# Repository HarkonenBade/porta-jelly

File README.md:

# porta-jelly

Rework of @cillian64 's excellent mini-jelly board (https://github.com/cillian64/cyberjelly/tree/master/mini_jellies/mini_jellies) tweaked to include an IP5306 based Lipo charge and boost setup to make a portable LED strip driving system with built in battery charging.

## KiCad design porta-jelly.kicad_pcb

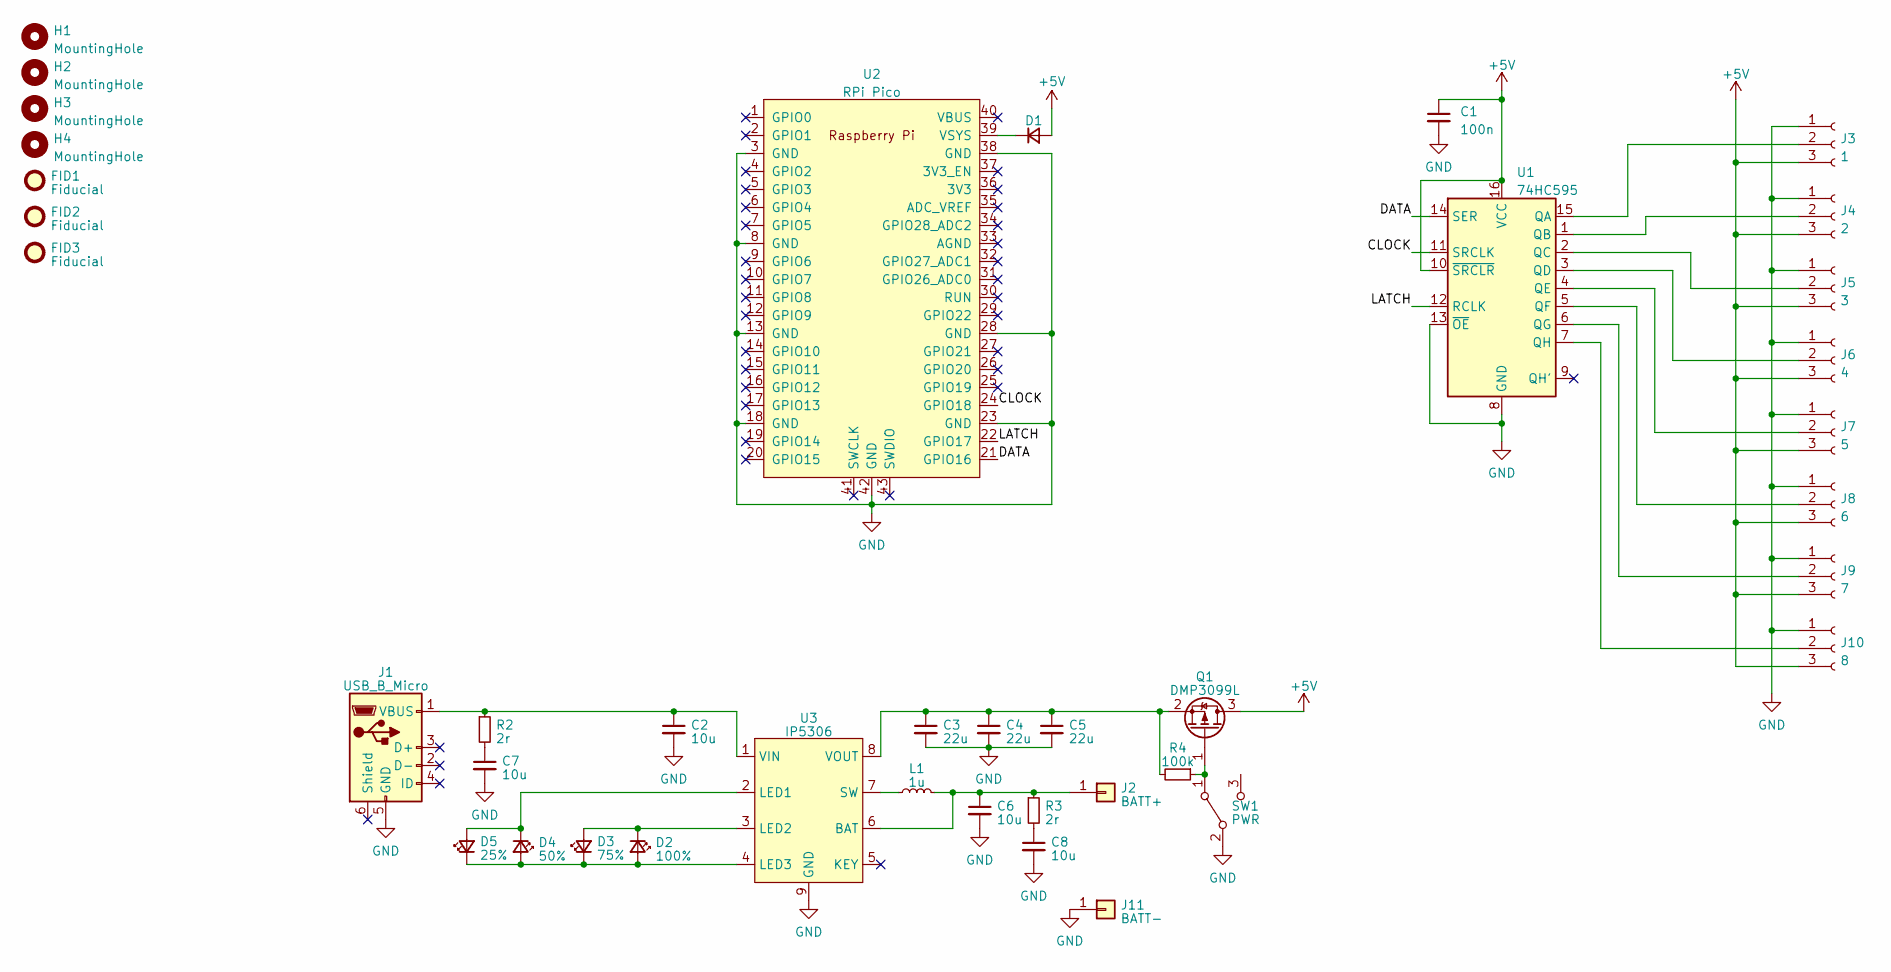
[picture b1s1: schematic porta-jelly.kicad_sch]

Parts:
C1: 100n; C_0603_1608Metric
C2, C6, C7, C8: 10u; C_0603_1608Metric; LCSC C19702
C3, C4, C5: 22u; C_0805_2012Metric; LCSC C159801
D1: D_Small; D_0805_2012Metric; LCSC C146335
D2: 100%; LED_0805_2012Metric; LCSC C497961
D3: 75%; LED_0805_2012Metric; LCSC C497961
D4: 50%; LED_0805_2012Metric; LCSC C497961
D5: 25%; LED_0805_2012Metric; LCSC C497961
FID1, FID2, FID3: Fiducial; Fiducial_1mm_Mask2mm
H1, H2, H3, H4: MountingHole; MountingHole_3.2mm_M3
J1: USB_B_Micro; USB_Micro-B_Molex-105017-0001; LCSC C136000
J2: BATT+; Bonded_Pad
J3: 1; Molex_KK-254_AE-6410-03A_1x03_P2.54mm_Vertical
J4: 2; Molex_KK-254_AE-6410-03A_1x03_P2.54mm_Vertical
J5: 3; Molex_KK-254_AE-6410-03A_1x03_P2.54mm_Vertical
J6: 4; Molex_KK-254_AE-6410-03A_1x03_P2.54mm_Vertical
J7: 5; Molex_KK-254_AE-6410-03A_1x03_P2.54mm_Vertical
J8: 6; Molex_KK-254_AE-6410-03A_1x03_P2.54mm_Vertical
J9: 7; Molex_KK-254_AE-6410-03A_1x03_P2.54mm_Vertical
J10: 8; Molex_KK-254_AE-6410-03A_1x03_P2.54mm_Vertical
J11: BATT-; Bonded_Pad
L1: 1u; LQH44PH1R0MPRL; LCSC C1857967
Q1: DMP3099L; SOT-23; LCSC C155244
R2, R3: 2r; R_0603_1608Metric; LCSC C307263
R4: 100k; R_0603_1608Metric
SW1: PWR; SK12D07VG5; LCSC C3020419
U1: 74HC595; SOIC-16_3.9x9.9mm_P1.27mm; LCSC C5947
U2: RPi Pico; RPi_Pico_SMD_TH
U3: IP5306; SOIC-8-1EP_3.9x4.9mm_P1.27mm_EP2.29x3mm_ThermalVias; LCSC C181692

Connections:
+5V: C1.1, D1.2 (A), J3.3, J4.3, J5.3, J6.3, J7.3, J8.3, J9.3, J10.3, Q1.3 (D), U1.10 (~SRCLR), U1.16 (VCC)
/CLOCK: U1.11 (SRCLK), U2.24 (GPIO18)
/DATA: U1.14 (SER), U2.21 (GPIO16)
/LATCH: U1.12 (RCLK), U2.22 (GPIO17)
GND: C1.2, C2.2, C3.2, C4.2, C5.2, C6.2, C7.2, C8.2, J1.5 (GND), J3.1, J4.1, J5.1, J6.1, J7.1, J8.1, J9.1, J10.1, J11.1, SW1.2 (B), U1.8 (GND), U1.13 (~OE), U2.3 (GND), U2.8 (GND), U2.13 (GND), U2.18 (GND), U2.23 (GND), U2.28 (GND), U2.38 (GND), U2.42 (GND), U3.9 (GND)
unnamed: C7.1, R2.2
unnamed: C8.1, R3.2
unnamed: D1.1 (K), U2.39 (VSYS)
unnamed: D2.2 (A), D3.1 (K), D4.2 (A), D5.1 (K), U3.4 (LED3)
unnamed: D2.1 (K), D3.2 (A), U3.3 (LED2)
unnamed: D4.1 (K), D5.2 (A), U3.2 (LED1)
unnamed: C2.1, J1.1 (VBUS), R2.1, U3.1 (VIN)
unnamed: C6.1, J2.1, L1.2, R3.1, U3.6 (BAT)
unnamed: J3.2, U1.15 (QA)
unnamed: J4.2, U1.1 (QB)
unnamed: J5.2, U1.2 (QC)
unnamed: J6.2, U1.3 (QD)
unnamed: J7.2, U1.4 (QE)
unnamed: J8.2, U1.5 (QF)
unnamed: J9.2, U1.6 (QG)
unnamed: J10.2, U1.7 (QH)
unnamed: Q1.1 (G), R4.1, SW1.1 (A)
unnamed: C3.1, C4.1, C5.1, Q1.2 (S), R4.2, U3.8 (VOUT)
unnamed: L1.1, U3.7 (SW)

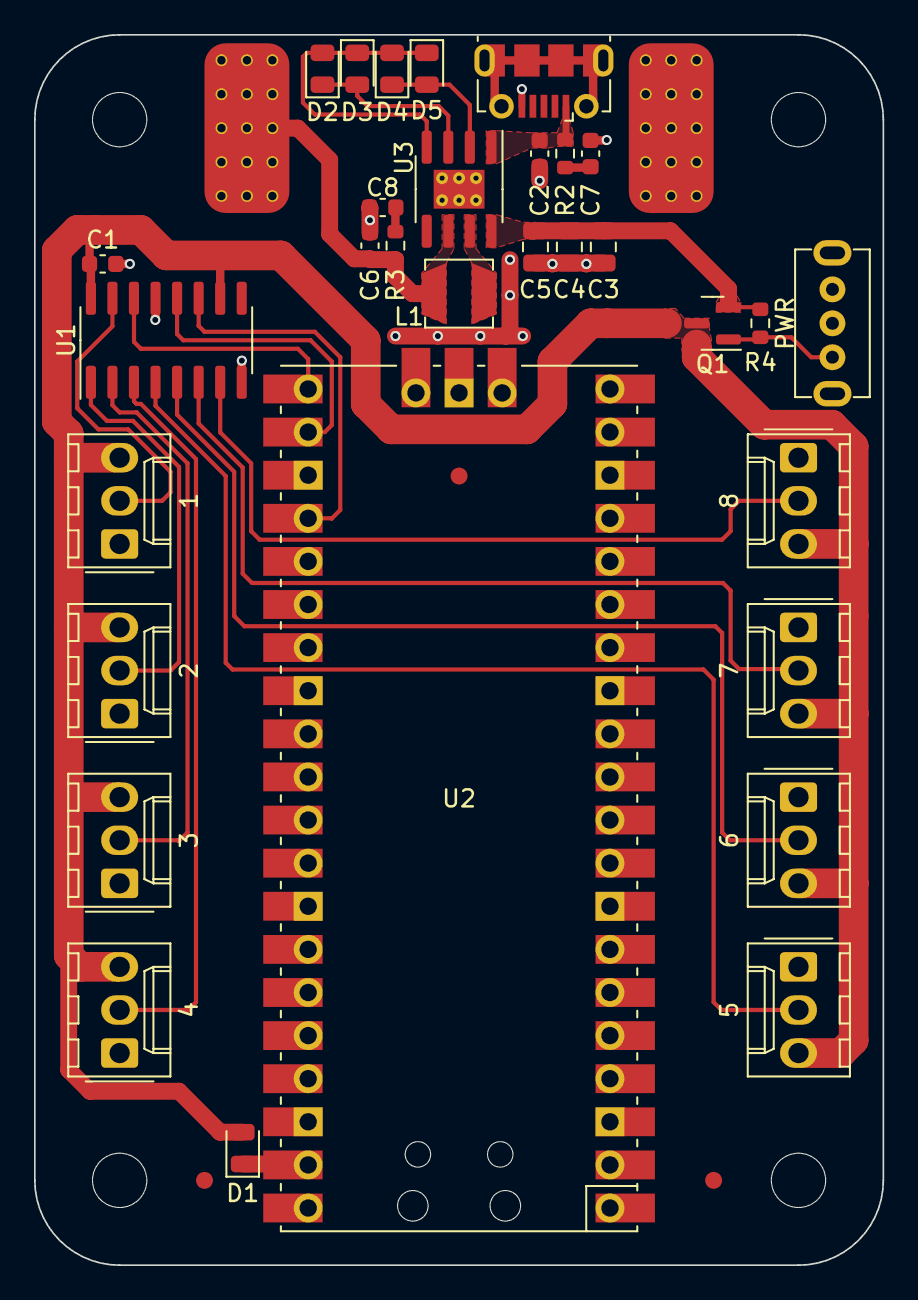
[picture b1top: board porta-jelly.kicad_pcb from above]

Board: 2 copper layers, 50.0 x 72.5 mm, 40 parts (0 on the bottom side), 24 nets.

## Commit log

2023-03-05 Initial Work - Schematic mostly complete sans finding specific parts for a few bits - PCB proposed layout of parts done, routing in progress
2023-03-15 Revised board design
2023-03-20 Final board, schematic updates, LCSC order codes
2023-03-20 Updated ibom
2023-03-20 Final gerbers and pos file
